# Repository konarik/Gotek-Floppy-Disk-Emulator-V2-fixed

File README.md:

Fixed PCB from original [Gotek-Floppy-Disk-Emulator-V2](https://github.com/RichardRozehnal/Gotek-Floppy-Disk-Emulator-V2):
* Add PCB edge cut for IDC 34-pin cable keying
* Change Buzzer type from Active to Passive (single click on drive motor step)
* Change "Buzzer_12x9.5RM7.6" footprint to "Buzzer_12x9.5RM6.5"

New modifications in V2.1:
* SMD Crystal
* 2nd SMD diode
* electrolytic capacitor replaced with 10uF MLCC
* decoupling capacitors moved close to the MCU
* added mounting holes
* generated production files for JLCPCB except through hole parts and 8bit SMD switch

# Gotek Floppy Disk Emulator V2

Emulátor disketové mechaniky starých počítačů a různých zařízení. Software se do počítače nahrává z obrazu originálního disku (např. ADF pro Amigu), který je uložen na USB flash disku. Tato verze hardwaru využívá firmware [FlashFloppy](https://github.com/keirf/FlashFloppy/wiki), který přidává spoustu nových funkcí a vylepšení oproti standardnímu Goteku. Na uvedém odkazu tvůrce, najdete detailní popisy všech funkcí a nastavení a také nejnovější firmware.

## Seznam součástek

| **Reference**                         | **Value**             | **Qty**  |
| ------------------------------------- | --------------------- | :----:   |
| <sup>BZ1                                   </sup>| <sup>5V Passive Buzzer 12mm   </sup>| <sup> 1 </sup> |
| <sup>C1,C2,C4,C7,C8,C9,C10,C12             </sup>| <sup>100nF                    </sup>| <sup> 8 </sup> |
| <sup>C3,C11                                </sup>| <sup>10uF                     </sup>| <sup> 2 </sup> |
| <sup>C5,C6                                 </sup>| <sup>22pF                     </sup>| <sup> 2 </sup> |
| <sup>C13                                   </sup>| <sup>10uF/16V                 </sup>| <sup> 1 </sup> |
| <sup>D1,D101                               </sup>| <sup>LED Green                </sup>| <sup> 2 </sup> |
| <sup>D2                                    </sup>| <sup>1N4148                   </sup>| <sup> 1 </sup> |
| <sup>H1                                    </sup>| <sup>Hole1                    </sup>| <sup> 1 </sup> |
| <sup>H2                                    </sup>| <sup>Hole2                    </sup>| <sup> 1 </sup> |
| <sup>H3                                    </sup>| <sup>Hole3                    </sup>| <sup> 1 </sup> |
| <sup>H4                                    </sup>| <sup>Hole4                    </sup>| <sup> 1 </sup> |
| <sup>J1                                    </sup>| <sup>Power Connector          </sup>| <sup> 1 </sup> |
| <sup>J2                                    </sup>| <sup>OLED Display 0.91" Modul </sup>| <sup> 1 </sup> |
| <sup>J3                                    </sup>| <sup>USB_A                    </sup>| <sup> 1 </sup> |
| <sup>J5                                    </sup>| <sup>Programming Connector    </sup>| <sup> 1 </sup> |
| <sup>J6                                    </sup>| <sup>Floppy Data Connector    </sup>| <sup> 1 </sup> |
| <sup>Q1                                    </sup>| <sup>MMBT2222                 </sup>| <sup> 1 </sup> |
| <sup>Q2,Q3,Q4,Q5,Q6,Q7                     </sup>| <sup>BSS123                   </sup>| <sup> 6 </sup> |
| <sup>R1                                    </sup>| <sup>4K7                      </sup>| <sup> 1 </sup> |
| <sup>R2,R3,R7,R8,R9,R10,R11,R12,R13,R14,R15,R16,R17,R18,R19,R20,R21,R22,R23,R24,R25,R26,R101,R102 </sup> | <sup>1K                      </sup> | <sup>24 </sup> |
| <sup>R4,R27                                </sup>| <sup>10K                      </sup> | <sup> 2 </sup> |
| <sup>R5,R6                                 </sup>| <sup>22R                      </sup> | <sup> 2 </sup> |
| <sup>SW1                                   </sup>| <sup>KY040 Rotary Encoder     </sup> | <sup> 1 </sup> |
| <sup>SW2                                   </sup>| <sup>DIP Switch               </sup> | <sup> 1 </sup> |
| <sup>U1                                    </sup>| <sup>AMS1117-3.3              </sup> | <sup> 1 </sup> |
| <sup>U2                                    </sup>| <sup>STM32F105RBTx            </sup> | <sup> 1 </sup> |
| <sup>U3                                    </sup>| <sup>STMPS2141                </sup> | <sup> 1 </sup> |
| <sup>U4                                    </sup>| <sup>74HCT04                  </sup> | <sup> 1 </sup> |
| <sup>Y1                                    </sup>| <sup>8MHz                     </sup> | <sup> 1 </sup> |

## Oživení

### Programování mikrokontroléru pomocí ST-Link V2

1. stáhněte si a nainstalujte flashovací program STM32-ST-Link Utility na webu [st.com](https://www.st.com/en/development-tools/stsw-link004.html).
2. propojte ST-Link V2 a Gotek V2 vývody SWCLK, SWDIO, GND a +3.3V
3. připojte ST-Link V2 k PC a spusťte flashovací program
4. připojte se na MCU přes menu Target/Connect
5. přes menu File/Open File vyberte soubor FF_Gotek-v3.20.hex (nebo jiný, který chcete nahrát do MCU)
6. spusťte flashování přes menu Target/Program & Verify a Start

### Nastavení DIP přepínače SW2

Pro Amigu, Atari ST a další počítače je nastavení:

| **sig** | **zap/vyp** | **funkce**                              |
| :-----: | :---------: | --------------------------------------- |
| DC1     | OFF         |                                         |
| DC2     | ON          |                                         |
| J5      | OFF         |                                         |
| JC      | OFF         |                                         |
| JB      | ON          | zapnutí/vypnutí emulace zvuku mechaniky |
| S0      | ON          |                                         |
| S1      | OFF         |                                         |

### Příprava USB flash disku a základní operace

1. USB flash disk naformátujte na FAT32 a nahrajte na něj obrazy disků, které budete chtít spouštět, např. ADF pro Amigu
2. připojte Gotek V2 s vloženým USB flash diskem k Amize (místo interního floppy disku), napájecí konektor je dobré před zapojením změřit, abyste do Goteku V2 nepustili 12V místo 5V, kvůli obrácení konektoru!
3. zapněte Amigu, na displeji se zobrazí první z podporovaných souborů, které jste nahráli a rotačním enkodérem mezi nima vybíráte
4. když najedete na soubor a počkáte 2s, tak se automaticky spustí (vloží do floppy mechaniky). Toto je možné v nastavení změnit, aby se automaticky nespouštěl. Potom bude pro vložení do mechaniky nutné stisknout rotační enkodér.
5. pokud chcete změnit orientaci posuvu v souborech (otáčení enkodéru doprava/doleva posouvat soubory nahoru/dolů), je to možné změnit v nastavení.
6. pokud se výběr souborů posune o jednu položku až při dvou nebo čtyřech krocích otočení enkodérem, je možné toto také upravit v nastavení

### Nastavení firmware

1. Gotek V2 funguje s defaultním nastavením i bez konfiguračního souboru
2. pokud však chcete určitou konfiguci změnit, vytvořte na USB flash disku adresář FF a do něj nahrajte konfigurační soubor FF.CFG
3. zrušení automatického spouštění souboru: autoselect-file-secs = 0
4. zrušení automatického vybrání adresáře: autoselect-folder-secs = 0
5. změna orientace posuvu v souborech: rotary = reverse
6. změna kroků enkodéru: rotary = half
7. je možné vybrat i více nastavení najednou, např.: rotary = reverse,half

## Další fotky (vzorky, úprava na BOT straně již není potřeba)

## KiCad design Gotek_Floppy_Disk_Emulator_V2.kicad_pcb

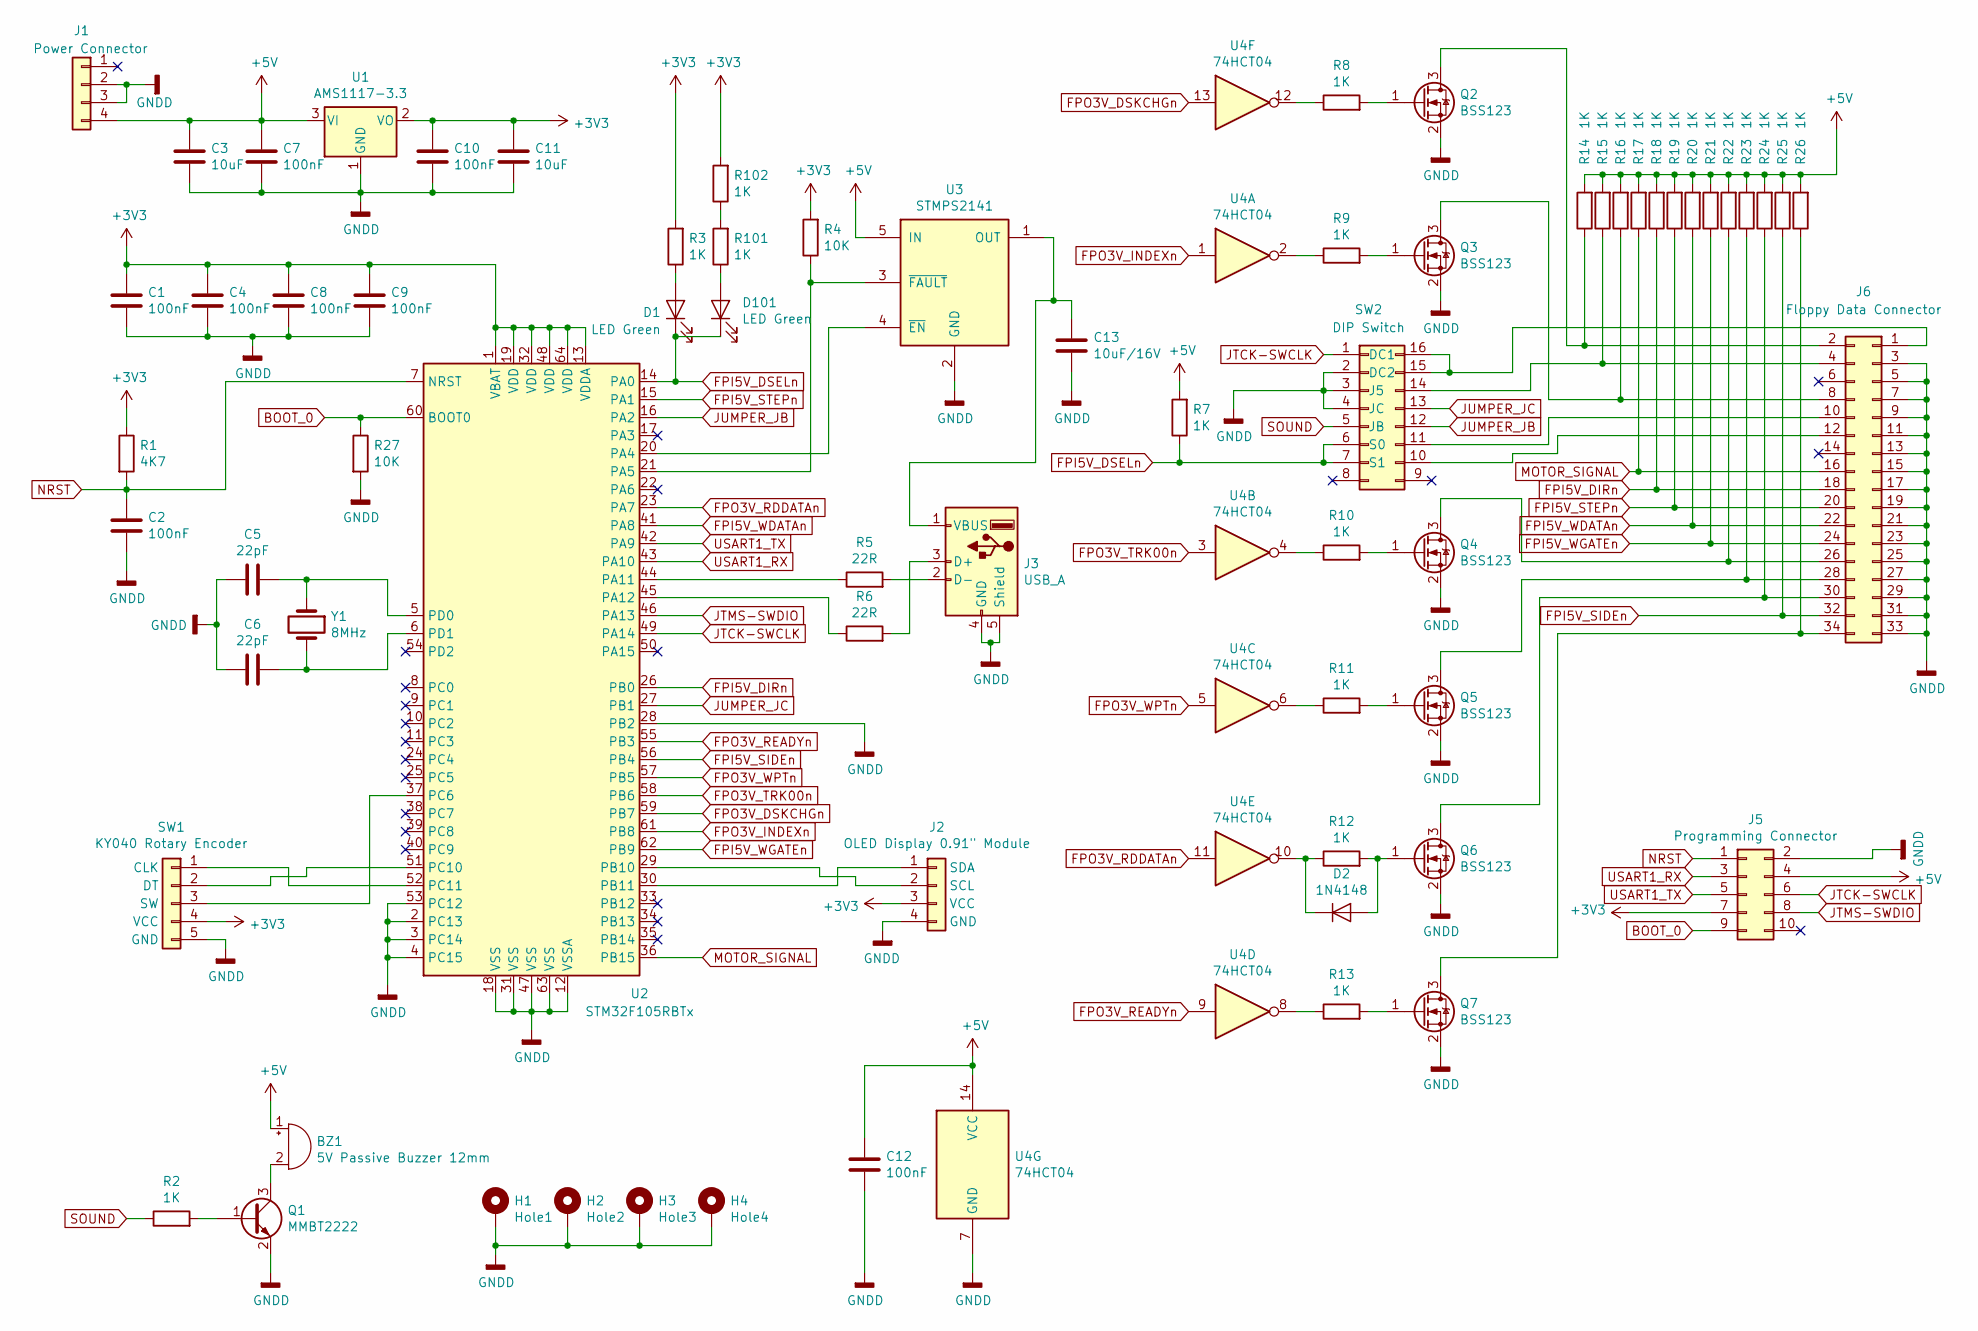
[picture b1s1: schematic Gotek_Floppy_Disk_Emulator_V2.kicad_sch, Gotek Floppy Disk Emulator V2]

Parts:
BZ1: 5V Passive Buzzer 12mm; Buzzer_12x9.5RM6.5
C1, C2, C4, C7, C8, C9, C10, C12: 100nF; C_1206_3216Metric
C3, C11: 10uF; C_1206_3216Metric
C5, C6: 22pF; C_0402_1005Metric
C13: 10uF/16V; C_1206_3216Metric
D1: LED Green; LED_D3.0mm
D2: 1N4148; D_SOD-123
D101: LED Green; LED_0805_2012Metric
H1: Hole1; MountingHole_3.2mm_M3_Pad_Via; Manufacturer_Part_Number DNP; LCSC DNP
H2: Hole2; MountingHole_3.2mm_M3_Pad_Via; Manufacturer_Part_Number DNP; LCSC DNP
H3: Hole3; MountingHole_3.2mm_M3_Pad_Via; Manufacturer_Part_Number DNP; LCSC DNP
H4: Hole4; MountingHole_3.2mm_M3_Pad_Via; Manufacturer_Part_Number DNP; LCSC DNP
J1: Power Connector; PinHeader_1x04_P2.54mm_Horizontal
J2: OLED Display 0.91" Module; OLED_Display_0.91_Module
J3: USB_A; USB_A_Stewart_SS-52100-001_Horizontal
J5: Programming Connector; PinHeader_2x05_P2.54mm_Vertical
J6: Floppy Data Connector; PinHeader_2x17_P2.54mm_Horizontal
Q1: MMBT2222; SOT-23
Q2, Q3, Q4, Q5, Q6, Q7: BSS123; SOT-23
R1: 4K7; R_1206_3216Metric
R2, R3, R7, R8, R9, R10, R11, R12, R13, R14, R15, R16, R17, R18, R19, R20, R21, R22, R23, R24, R25, R26, R101, R102: 1K; R_1206_3216Metric
R4, R27: 10K; R_1206_3216Metric
R5, R6: 22R; R_1206_3216Metric
SW1: KY040 Rotary Encoder; PinHeader_1x05_P2.54mm_Vertical
SW2: DIP Switch; SW_DIP_SPSTx08_Slide_6.7x21.88mm_W8.61mm_P2.54mm_LowProfile
U1: AMS1117-3.3; SOT-223-3_TabPin2
U2: STM32F105RBTx; LQFP-64_10x10mm_P0.5mm
U3: STMPS2141; SOT-23-5
U4: 74HCT04; SOIC-14_3.9x8.7mm_P1.27mm
Y1: 8MHz; Crystal_SMD_5032-2Pin_5.0x3.2mm

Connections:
+3V3: C1.1, C4.1, C8.1, C9.1, C10.1, C11.1, J2.3 (VCC), J5.7, R1.1, R3.2, R4.2, R102.2, SW1.4 (VCC), U1.2 (VO), U2.1 (VBAT), U2.13 (VDDA), U2.19 (VDD), U2.32 (VDD), U2.48 (VDD), U2.64 (VDD)
+5V: BZ1.1 (-), C3.1, C7.1, C12.1, J1.4, J5.4, R7.2, R14.2, R15.2, R16.2, R17.2, R18.2, R19.2, R20.2, R21.2, R22.2, R23.2, R24.2, R25.2, R26.2, U1.3 (VI), U3.5 (IN), U4.14 (VCC)
BOOT_0: J5.9, R27.1, U2.60 (BOOT0)
FPI5V_DIRn: J6.18, R18.1, U2.26 (PB0)
FPI5V_DSELn: D1.1 (K), D101.1 (K), R7.1, SW2.6 (S0), SW2.7 (S1), U2.14 (PA0)
FPI5V_SIDEn: J6.32, R25.1, U2.56 (PB4)
FPI5V_STEPn: J6.20, R19.1, U2.15 (PA1)
FPI5V_WDATAn: J6.22, R20.1, U2.41 (PA8)
FPI5V_WGATEn: J6.24, R21.1, U2.62 (PB9)
FPO3V_DSKCHGn: U2.59 (PB7), U4.13
FPO3V_INDEXn: U2.61 (PB8), U4.1
FPO3V_RDDATAn: U2.23 (PA7), U4.11
FPO3V_READYn: U2.55 (PB3), U4.9
FPO3V_TRK00n: U2.58 (PB6), U4.3
FPO3V_WPTn: U2.57 (PB5), U4.5
GNDD: C1.2, C2.2, C3.2, C4.2, C5.2, C6.2, C7.2, C8.2, C9.2, C10.2, C11.2, C12.2, C13.2, H1.1, H2.1, H3.1, H4.1, J1.2, J1.3, J2.4 (GND), J3.4 (GND), J3.5 (Shield), J5.2, J6.3, J6.5, J6.7, J6.9, J6.11, J6.13, J6.15, J6.17, J6.19, J6.21, J6.23, J6.25, J6.27, J6.29, J6.31, J6.33, Q1.2 (E), Q2.2 (S), Q3.2 (S), Q4.2 (S), Q5.2 (S), Q6.2 (S), Q7.2 (S), R27.2, SW1.5 (GND), SW2.2 (DC2), SW2.3 (J5), SW2.4 (JC), U1.1 (GND), U2.2 (PC13), U2.3 (PC14), U2.4 (PC15), U2.12 (VSSA), U2.18 (VSS), U2.28 (PB2), U2.31 (VSS), U2.47 (VSS), U2.53 (PC12), U2.63 (VSS), U3.2 (GND), U4.7 (GND)
JTCK-SWCLK: J5.6, SW2.1 (DC1), U2.49 (PA14)
JTMS-SWDIO: J5.8, U2.46 (PA13)
JUMPER_JB: SW2.12, U2.16 (PA2)
JUMPER_JC: SW2.13, U2.27 (PB1)
MOTOR_SIGNAL: J6.16, R17.1, U2.36 (PB15)
NRST: C2.1, J5.1, R1.2, U2.7 (NRST)
unnamed: BZ1.2 (+), Q1.3 (C)
unnamed: D1.2 (A), R3.1
unnamed: D2.2 (A), Q6.1 (G), R12.2
unnamed: D2.1 (K), R12.1, U4.10
unnamed: D101.2 (A), R101.1
unnamed: J2.2 (SCL), U2.29 (PB10)
unnamed: J2.1 (SDA), U2.30 (PB11)
unnamed: J3.3 (D+), R6.2
unnamed: J3.2 (D-), R5.2
unnamed: C13.1, J3.1 (VBUS), U3.1 (OUT)
unnamed: J6.1, SW2.15, SW2.16
unnamed: J6.2, Q2.3 (D), R14.1
unnamed: J6.4, R15.1, SW2.14
unnamed: J6.8, Q3.3 (D), R16.1
unnamed: J6.10, SW2.11
unnamed: J6.12, SW2.10
unnamed: J6.26, Q4.3 (D), R22.1
unnamed: J6.28, Q5.3 (D), R23.1
unnamed: J6.30, Q6.3 (D), R24.1
unnamed: J6.34, Q7.3 (D), R26.1
unnamed: Q1.1 (B), R2.2
unnamed: Q2.1 (G), R8.2
unnamed: Q3.1 (G), R9.2
unnamed: Q4.1 (G), R10.2
unnamed: Q5.1 (G), R11.2
unnamed: Q7.1 (G), R13.2
unnamed: R8.1, U4.12
unnamed: R9.1, U4.2
unnamed: R10.1, U4.4
unnamed: R11.1, U4.6
unnamed: R13.1, U4.8
unnamed: R101.2, R102.1
unnamed: SW1.1 (CLK), U2.52 (PC11)
unnamed: SW1.2 (DT), U2.51 (PC10)
unnamed: SW1.3 (SW), U2.37 (PC6)
unnamed: U2.20 (PA4), U3.4 (~EN)
unnamed: R4.1, U2.21 (PA5), U3.3 (~FAULT)
unnamed: R5.1, U2.44 (PA11)
unnamed: R6.1, U2.45 (PA12)
unnamed: C5.1, U2.5 (PD0), Y1.1
unnamed: C6.1, U2.6 (PD1), Y1.2
SOUND: R2.1, SW2.5 (JB)
USART1_RX: J5.3, U2.43 (PA10)
USART1_TX: J5.5, U2.42 (PA9)

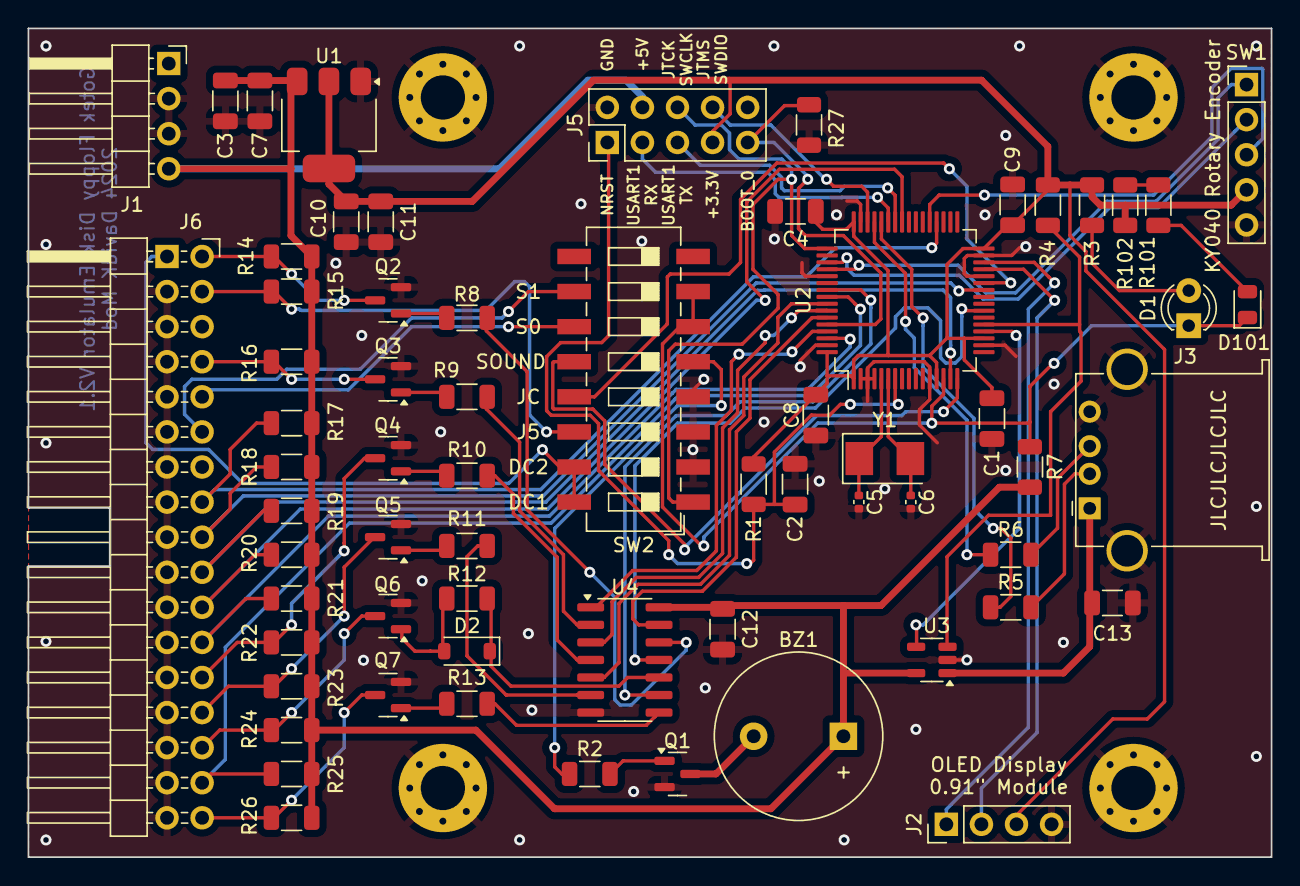
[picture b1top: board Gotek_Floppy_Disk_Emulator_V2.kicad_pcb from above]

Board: 2 copper layers, 90.0 x 60.0 mm, 69 parts (0 on the bottom side), 66 nets.

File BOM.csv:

"Reference","Value","Datasheet","Footprint","Qty","DNP"
"BZ1","5V Passive Buzzer 12mm","~","Gotek_Floppy_Disk_Emulator_V2:Buzzer_12x9.5RM6.5","1",""
"C1,C2,C4,C7,C8,C9,C10,C12","100nF","~","Capacitor_SMD:C_1206_3216Metric","8",""
"C3,C11","10uF","~","Capacitor_SMD:C_1206_3216Metric","2",""
"C5,C6","22pF","~","Capacitor_SMD:C_0402_1005Metric","2",""
"C13","10uF/16V","~","Capacitor_SMD:C_1206_3216Metric","1",""
"D1,D101","LED Green","~","-- mixed values --","2",""
"D2","1N4148","~","Diode_SMD:D_SOD-123","1",""
"H1","Hole1","DNP","MountingHole:MountingHole_3.2mm_M3_Pad_Via","1",""
"H2","Hole2","DNP","MountingHole:MountingHole_3.2mm_M3_Pad_Via","1",""
"H3","Hole3","DNP","MountingHole:MountingHole_3.2mm_M3_Pad_Via","1",""
"H4","Hole4","DNP","MountingHole:MountingHole_3.2mm_M3_Pad_Via","1",""
"J1","Power Connector","~","Gotek_Floppy_Disk_Emulator_V2:PinHeader_1x04_P2.54mm_Horizontal","1",""
"J2","OLED Display 0.91"" Module","~","Gotek_Floppy_Disk_Emulator_V2:OLED_Display_0.91_Module","1",""
"J3","USB_A"," ~","Gotek_Floppy_Disk_Emulator_V2:USB_A_Stewart_SS-52100-001_Horizontal","1",""
"J5","Programming Connector","~","Connector_PinHeader_2.54mm:PinHeader_2x05_P2.54mm_Vertical","1",""
"J6","Floppy Data Connector","~","Gotek_Floppy_Disk_Emulator_V2:PinHeader_2x17_P2.54mm_Horizontal","1",""
"Q1","MMBT2222","~","Package_TO_SOT_SMD:SOT-23","1",""
"Q2,Q3,Q4,Q5,Q6,Q7","BSS123","http://www.diodes.com/assets/Datasheets/ds30366.pdf","Package_TO_SOT_SMD:SOT-23","6",""
"R1","4K7","~","Resistor_SMD:R_1206_3216Metric","1",""
"R2,R3,R7,R8,R9,R10,R11,R12,R13,R14,R15,R16,R17,R18,R19,R20,R21,R22,R23,R24,R25,R26,R101,R102","1K","~","Resistor_SMD:R_1206_3216Metric","24",""
"R4,R27","10K","~","Resistor_SMD:R_1206_3216Metric","2",""
"R5,R6","22R","~","Resistor_SMD:R_1206_3216Metric","2",""
"SW1","KY040 Rotary Encoder","~","Connector_PinHeader_2.54mm:PinHeader_1x05_P2.54mm_Vertical","1",""
"SW2","DIP Switch","~","Button_Switch_SMD:SW_DIP_SPSTx08_Slide_6.7x21.88mm_W8.61mm_P2.54mm_LowProfile","1",""
"U1","AMS1117-3.3","http://www.advanced-monolithic.com/pdf/ds1117.pdf","Package_TO_SOT_SMD:SOT-223-3_TabPin2","1",""
"U2","STM32F105RBTx","http://www.st.com/st-web-ui/static/active/en/resource/techni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","Gotek_Floppy_Disk_Emulator_V2:LQFP-64_10x10mm_P0.5mm","1",""
"U3","STMPS2141","","Package_TO_SOT_SMD:SOT-23-5","1",""
"U4","74HCT04","https://assets.nexperia.com/documents/data-sheet/74HC_HCT04.pdf","Package_SO:SOIC-14_3.9x8.7mm_P1.27mm","1",""
"Y1","8MHz","~","Crystal:Crystal_SMD_5032-2Pin_5.0x3.2mm","1",""

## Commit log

2024-04-19 Updated to KiCAD version 6
2024-04-19 KiCAD v8 version
2024-04-19 Production files generated
    Some parts were exchanged for SMD mounted. For production generation was used Bouni/kicad-jlcpcb-tools plugin.
2024-04-19 Removed old KiCAD files
2024-04-19 Schematic updated
2024-04-21 V2.1
    Production files for JLCPCB excluding through hole parts and 8bit switch. Capacitors moved close to the voltage input pins of the MCU.
2024-04-21 Wider 5V patch for USB
2024-04-21 bom generated
